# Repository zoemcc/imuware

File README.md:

imuware
=======

Hardware code for wearable and chainable IMU's, and more to come!

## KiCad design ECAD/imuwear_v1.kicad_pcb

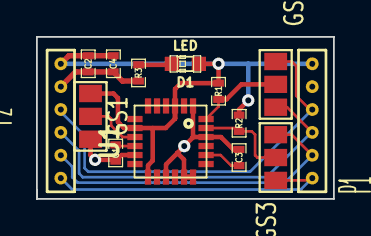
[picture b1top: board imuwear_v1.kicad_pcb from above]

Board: 2 copper layers, 16.5 x 9.0 mm, 14 parts (0 on the bottom side), 12 nets.

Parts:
C1, C2: 0.1uF; SM0402_c
C3: 2.2nF; SM0402_c
C4: 10nF; SM0402_c
D1: LED; LED-0603
GS1, GS2, GS3: GS3
P1, P2: CONN_6; SIL-6-MINIMUM
R1, R2: 10K; SM0402_r
R3: 33; SM0402_r
U1: MPU_9150; MPU9150_SMALL_KEEPOUT

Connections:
/ADDR: GS1.2, U1.9
/SCL: GS3.2, R2.2, U1.23
/SCL1: GS3.1, P1.5, P2.5
/SCL2: GS3.3, P1.6, P2.6
/SDA: GS2.2, R1.2, U1.24
/SDA1: GS2.1, P1.3, P2.3
/SDA2: GS2.3, P1.4, P2.4
/VCC: C2.2, C4.2, D1.1, GS1.1, P1.1, P2.1, R1.1, R2.1, U1.3, U1.8, U1.13
GND: C1.2, C2.1, C3.2, C4.1, GS1.3, P1.2, P2.2, R3.2, U1.1, U1.11, U1.15, U1.17, U1.18, U1.22
unnamed: D1.2, R3.1
unnamed: C1.1, U1.10
unnamed: C3.1, U1.20

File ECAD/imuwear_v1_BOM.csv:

ref	value	footprint
C1	0.1uF	~
C2	0.1uF	~
C3	2.2nF	~
C4	10nF	~
D1	LED	~
GS1	GS3	
GS2	GS3	
GS3	GS3	
P1	CONN_6	
P2	CONN_6	
R1	10K	~
R2	10K	~
R3	33	~
U1	MPU_9150	~

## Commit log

2014-04-20 Added gitmodules and submodule KiCad-Libraries
2014-04-20 Added init KiCAD project and Schematic
    Added mpu-9150, make sure library is loaded to load schematic
2014-04-20 Updated Schematic, mostly finished wiring up MPU9150
2014-04-22 Added initial Netlist, Board, and Footprint Modules
    Added footprints for 6 pin SMD and smallest throughole possible.
2014-04-24 Initial layout before routing PCB
    board is 16.5mm x 9mm
2014-04-24 Finished first layout
    need to clean up ground plane and silkscreen
2014-04-24 Added picture of first layout
2014-04-25 Final Layout of v1, added gerbers
    Final layout, added gerbers, pdf, and modules for OSH symbol
2014-05-23 Added Front solder paste
2014-05-23 Added solder_paste_stencil.pdf
2014-05-23 autosave stuffs
2014-05-23 solder_paste_stencil.svg
2014-05-23 Added solderpaste top svg
2014-05-23 added corrected svg
2014-05-23 added dxf and png of solder paste top
2014-05-30 Added initial CAD model for IMUring + Hand Model
2014-05-31 Added DistalRing_v2 and MiddleRing_v1
2014-06-02 Added Solder Paste stencils for laser cut
    added 5 mil clearance for laser cut with universal laser
2014-06-10 Added DistalRing_Colin_v3
    Spring loaded ring
